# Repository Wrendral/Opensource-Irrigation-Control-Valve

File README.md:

# Opensource-Irrigation-Control-Valve

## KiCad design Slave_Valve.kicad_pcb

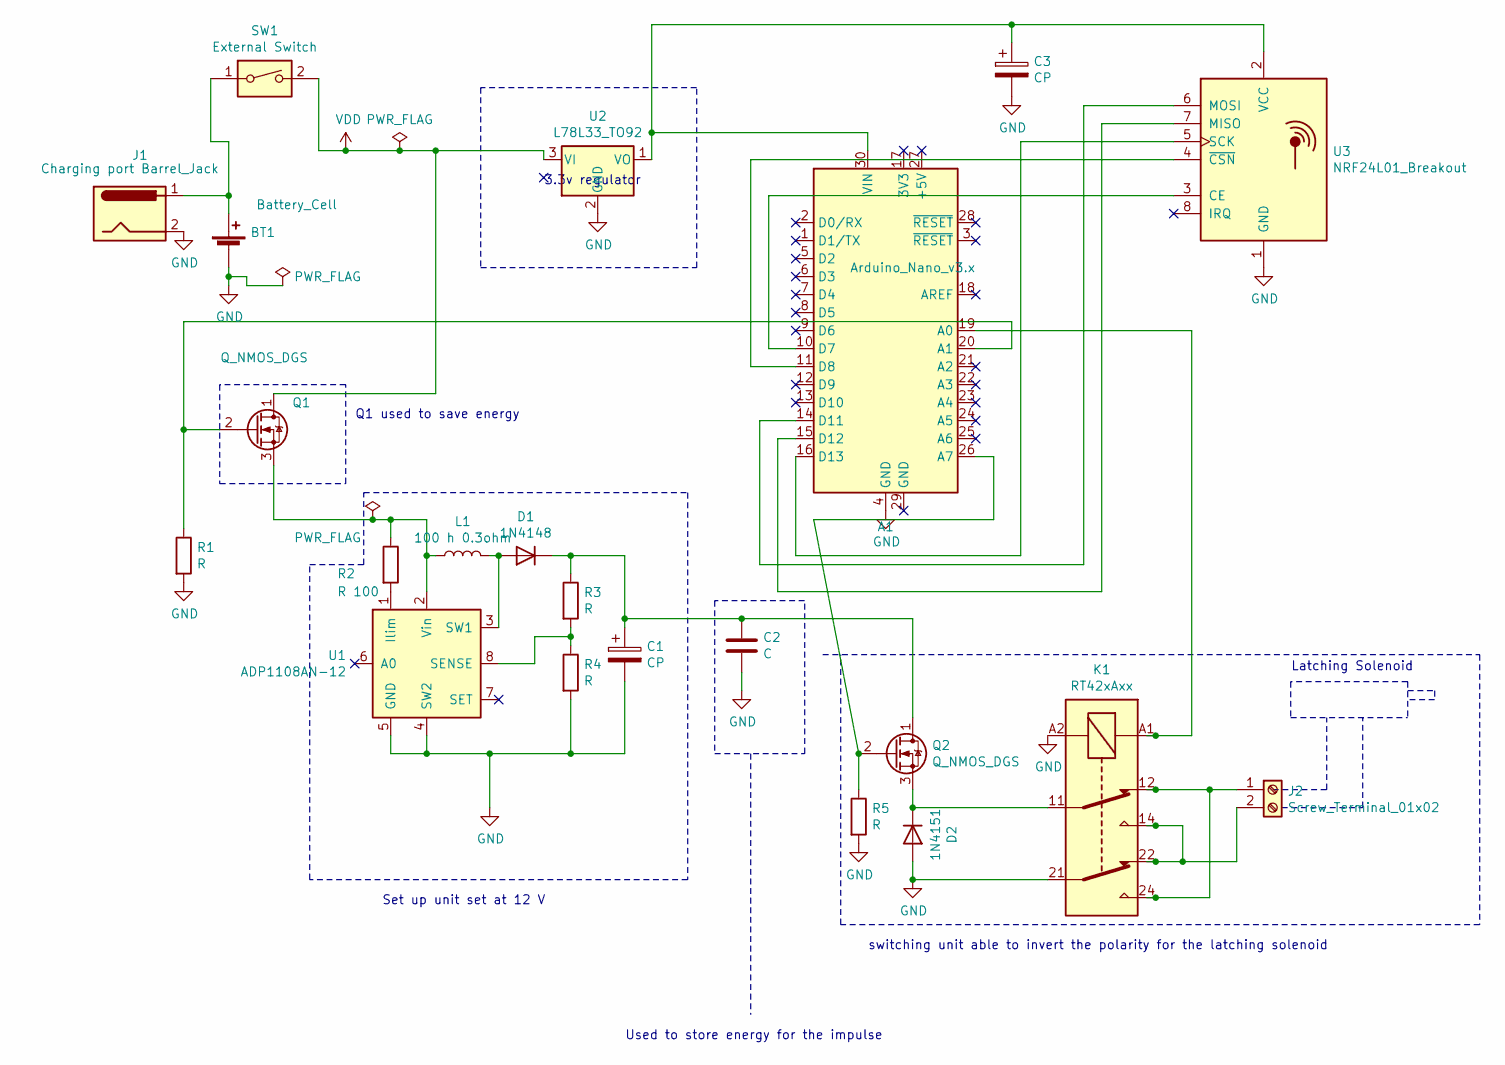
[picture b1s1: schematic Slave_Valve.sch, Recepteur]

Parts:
A1: Arduino_Nano_v3.x; Arduino_Nano_WithMountingHoles
BT1: Battery_Cell; BatteryHolder_Keystone_1042_1x18650
C1, C3: CP; CP_Radial_D10.0mm_P3.80mm
C2: C; C_Radial_D12.5mm_H25.0mm_P5.00mm
D1: 1N4148; D_DO-35_SOD27_P7.62mm_Horizontal
D2: 1N4151; D_DO-35_SOD27_P7.62mm_Horizontal
J1: Charging port Barrel_Jack; BarrelJack_CUI_PJ-063AH_Horizontal
J2: Screw_Terminal_01x02; TerminalBlock_bornier-3_P5.08mm
K1: RT42xAxx; Relay_DPDT_Schrack-RT2-FormC_RM5mm
L1: 100 h 0.3ohm; L_Radial_D7.0mm_P3.00mm
Q1, Q2: Q_NMOS_DGS; TO-220-3_Vertical
R1, R3, R4, R5: R; R_Axial_DIN0207_L6.3mm_D2.5mm_P7.62mm_Horizontal
R2: R 100; R_Axial_DIN0207_L6.3mm_D2.5mm_P7.62mm_Horizontal
SW1: External Switch; SolderWire-0.5sqmm_1x02_P4.8mm_D0.9mm_OD2.3mm
U1: ADP1108AN-12; DIP-8_W7.62mm
U2: L78L33_TO92; TO-92_Inline
U3: NRF24L01_Breakout; nRF24L01_Breakout

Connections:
GND: A1.4 (GND), BT1.2 (-), C1.2, C2.2, C3.2, D2.2 (A), J1.2, K1.21, K1.A2, R1.2, R4.2, R5.2, U1.4 (SW2), U1.5 (GND), U2.2 (GND), U3.1 (GND)
unnamed: A1.10 (D7), U3.3 (CE)
unnamed: A1.11 (D8), U3.4 (~CSN)
unnamed: A1.14 (D11), U3.6 (MOSI)
unnamed: A1.15 (D12), U3.7 (MISO)
unnamed: A1.16 (D13), U3.5 (SCK)
unnamed: A1.19 (A0), K1.A1
unnamed: A1.20 (A1), Q1.2 (G), R1.1
unnamed: A1.26 (A7), Q2.2 (G), R5.1
unnamed: A1.30 (VIN), C3.1, U2.1 (VO), U3.2 (VCC)
unnamed: BT1.1 (+), J1.1, SW1.1
unnamed: C1.1, C2.1, D1.1 (K), Q2.1 (D), R3.1
unnamed: D1.2 (A), L1.2, U1.3 (SW1)
unnamed: D2.1 (K), K1.11, Q2.3 (S)
unnamed: J2.1, K1.12, K1.24
unnamed: J2.2, K1.14, K1.22
unnamed: L1.1, Q1.3 (S), R2.1, U1.2 (Vin)
unnamed: R2.2, U1.1 (Ilim)
unnamed: R3.2, R4.1, U1.8 (SENSE)
VDD: Q1.1 (D), SW1.2, U2.3 (VI)

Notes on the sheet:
3.3v regulator
Set up unit set at 12 V
switching unit able to invert the polarity for the latching solenoid
Latching Solenoid
Q1 used to save energy
Used to store energy for the impulse

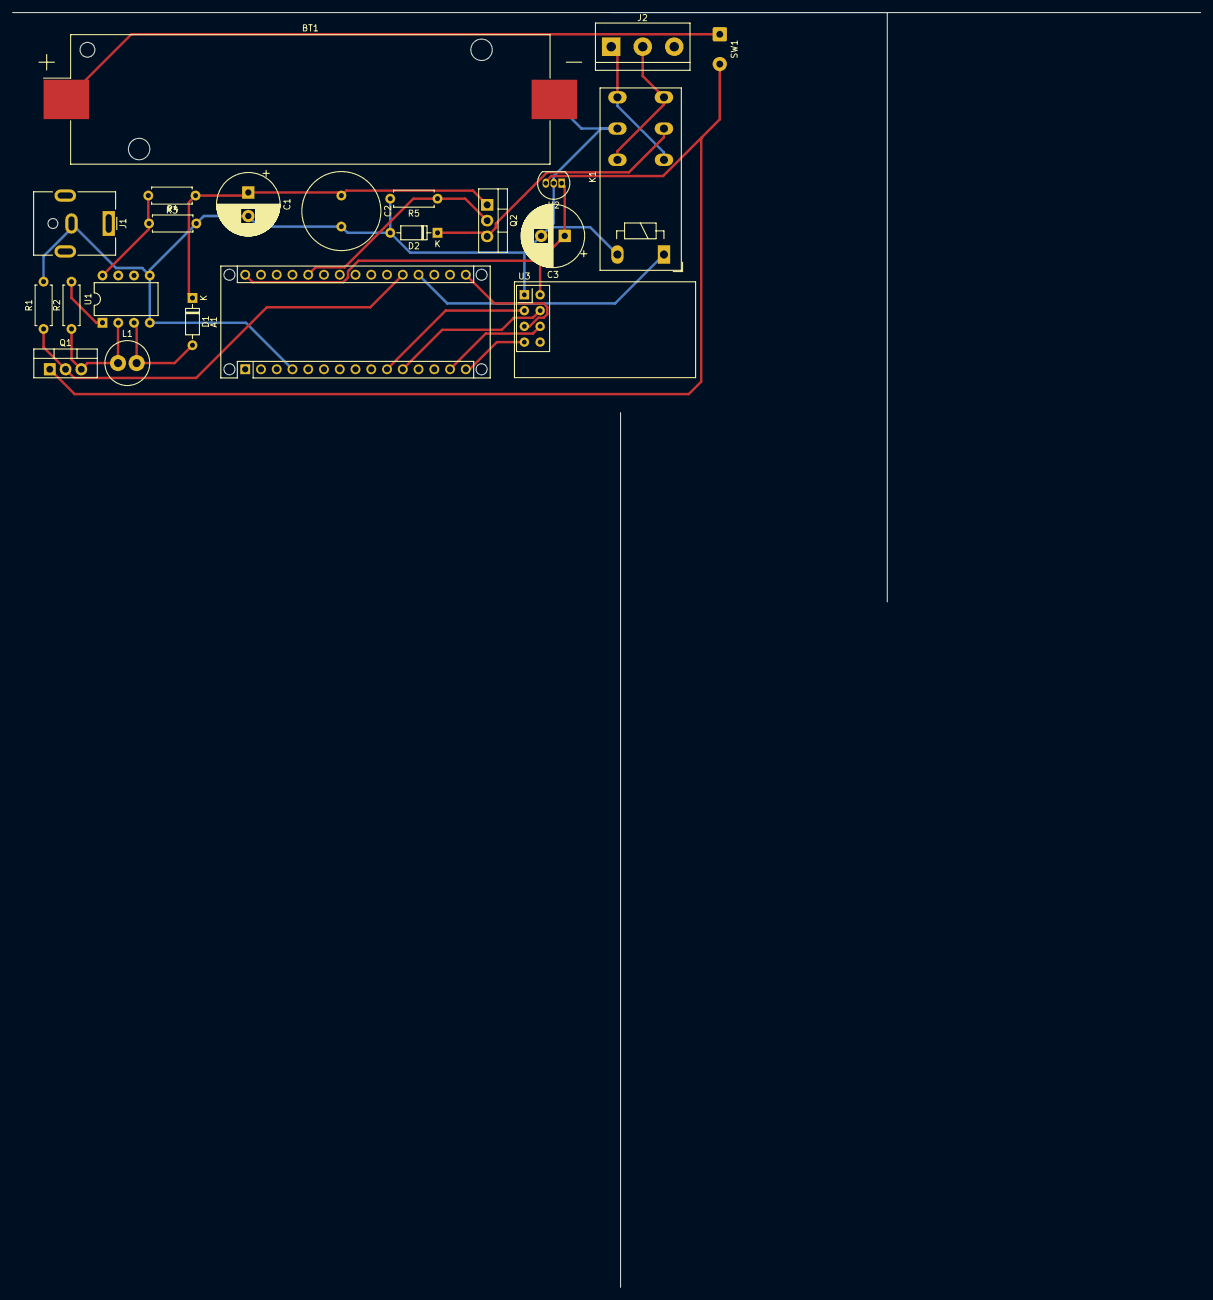
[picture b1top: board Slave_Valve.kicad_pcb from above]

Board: 2 copper layers, 191.5 x 205.5 mm, 22 parts (0 on the bottom side), 20 nets.
